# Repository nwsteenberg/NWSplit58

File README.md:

# NWSplit58 

A 58 key split keyboard made for Nordic ISO layout. The keyboard layout, case, PCB and plate are all designed from scratch. Small additions like ports for the case is done in Blender, but 99% is done in Ergogen.

Firmware is done in KMK with the layout being very standard Nordic layout, with additional thumb keys and HomeTab mods to remove the command row. 

Head over i [WALKTHROUGH.md](WALKTHROUGH.md) to read about my process of creating the keyboard.

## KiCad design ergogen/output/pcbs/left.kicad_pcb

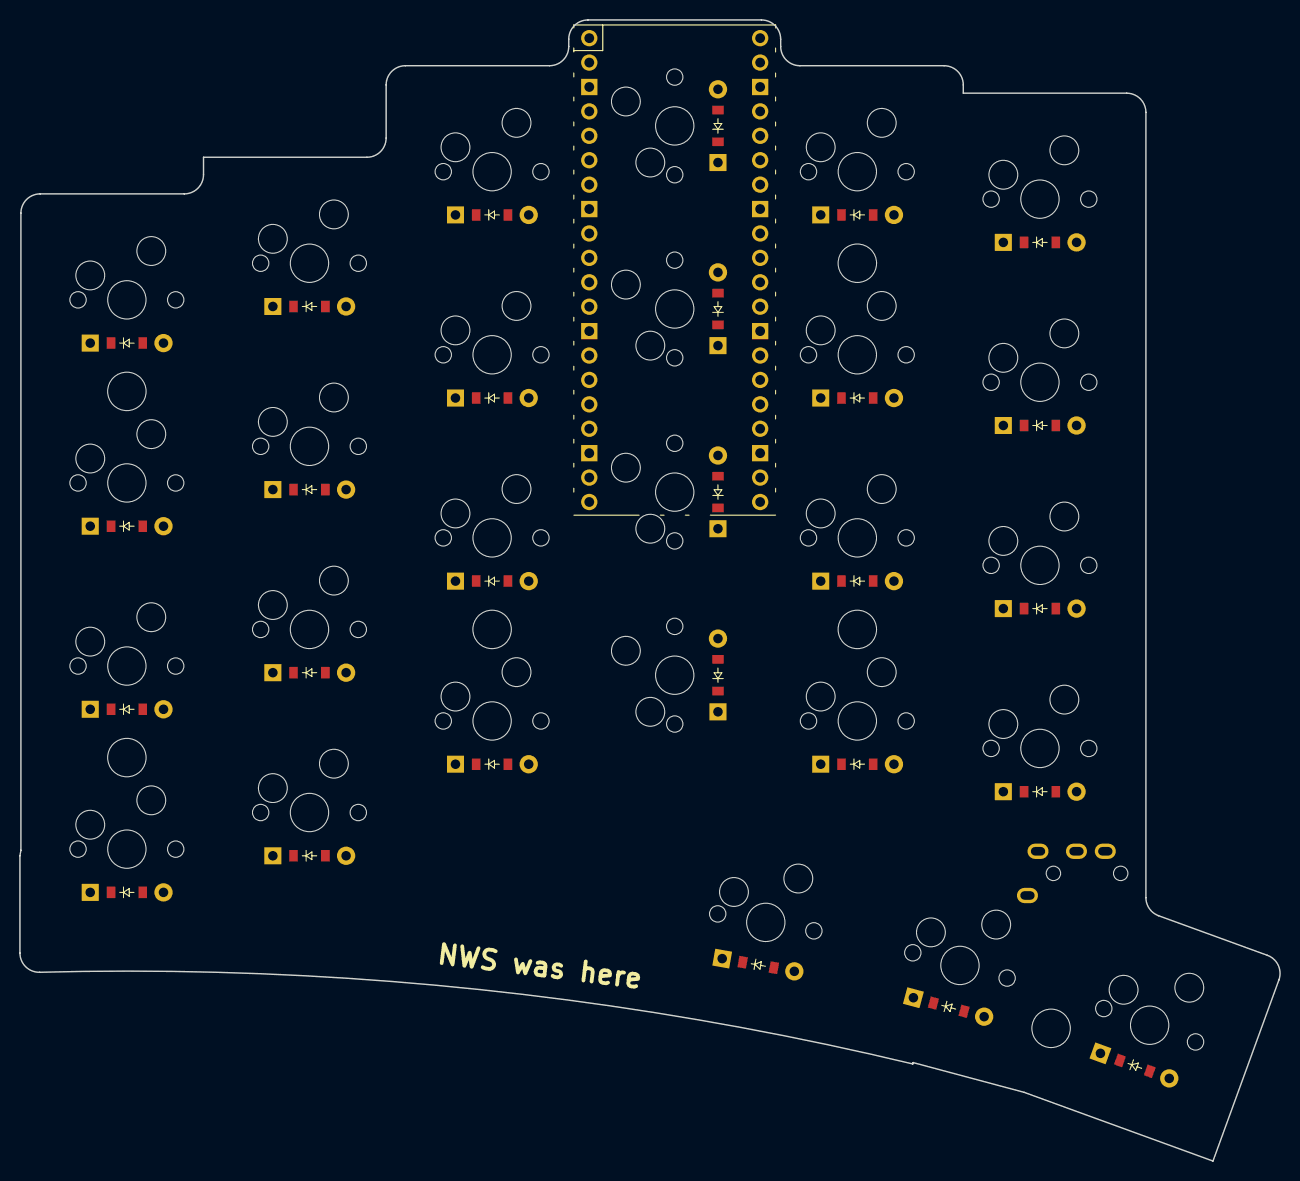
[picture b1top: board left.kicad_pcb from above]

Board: 2 copper layers, 131.1 x 118.7 mm, 56 parts (1 on the bottom side), 42 nets, no tracks yet.

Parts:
D1, D2, D3, D4, D5, D6, D7, D8, D9, D10, D11, D12, D13, D14, D15, D16, D17, D18, D19, D20, D21, D22, D23, D24, D25, D26, D27: ComboDiode
S1, S2, S3, S4, S5, S6, S7, S8, S9, S10, S11, S12, S13, S14, S15, S16, S17, S18, S19, S20, S21, S22, S23, S24, S25, S26, S27: MX
TRRS1: trrs_pj320a
_1: RPi_Pico_SMD_TH

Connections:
3V3: TRRS1.4, _1.36
GND: TRRS1.2, _1.3, _1.8, _1.13, _1.18, _1.23, _1.28, _1.38
GP0: TRRS1.5, _1.1
GP1: TRRS1.3, _1.2
GP6: S17.1, S18.1, S19.1, S20.1, S23.1, _1.9
GP7: S13.1, S14.1, S15.1, S16.1, S22.1, _1.10
GP8: S21.1, S24.1, S25.1, S26.1, S27.1, _1.11
GP9: S9.1, S10.1, S11.1, S12.1, _1.12
GP10: S5.1, S6.1, S7.1, S8.1, _1.14
GP11: S1.1, S2.1, S3.1, S4.1, _1.15
GP16: D21.1, D22.1, D23.1, _1.21
GP17: D1.1, D5.1, D9.1, D13.1, D17.1, D24.1, _1.22
GP18: D2.1, D6.1, D10.1, D14.1, D18.1, D25.1, _1.24
GP19: D3.1, D7.1, D11.1, D15.1, D19.1, D26.1, _1.25
GP20: D4.1, D8.1, D12.1, D16.1, D20.1, D27.1, _1.26
center_only: D22.2, S22.2
index_bottom: D13.2, S13.2
index_home: D14.2, S14.2
index_num: D16.2, S16.2
index_top: D15.2, S15.2
inner_bottom: D17.2, S17.2
inner_home: D18.2, S18.2
inner_num: D20.2, S20.2
inner_top: D19.2, S19.2
middle_bottom: D24.2, S24.2
middle_home: D25.2, S25.2
middle_num: D27.2, S27.2
middle_top: D26.2, S26.2
outer_bottom: D1.2, S1.2
outer_home: D2.2, S2.2
outer_num: D4.2, S4.2
outer_top: D3.2, S3.2
pinky_bottom: D5.2, S5.2
pinky_home: D6.2, S6.2
pinky_num: D8.2, S8.2
pinky_top: D7.2, S7.2
reach_only: D23.2, S23.2
ring_bottom: D9.2, S9.2
ring_home: D10.2, S10.2
ring_num: D12.2, S12.2
ring_top: D11.2, S11.2
tuck_only: D21.2, S21.2
